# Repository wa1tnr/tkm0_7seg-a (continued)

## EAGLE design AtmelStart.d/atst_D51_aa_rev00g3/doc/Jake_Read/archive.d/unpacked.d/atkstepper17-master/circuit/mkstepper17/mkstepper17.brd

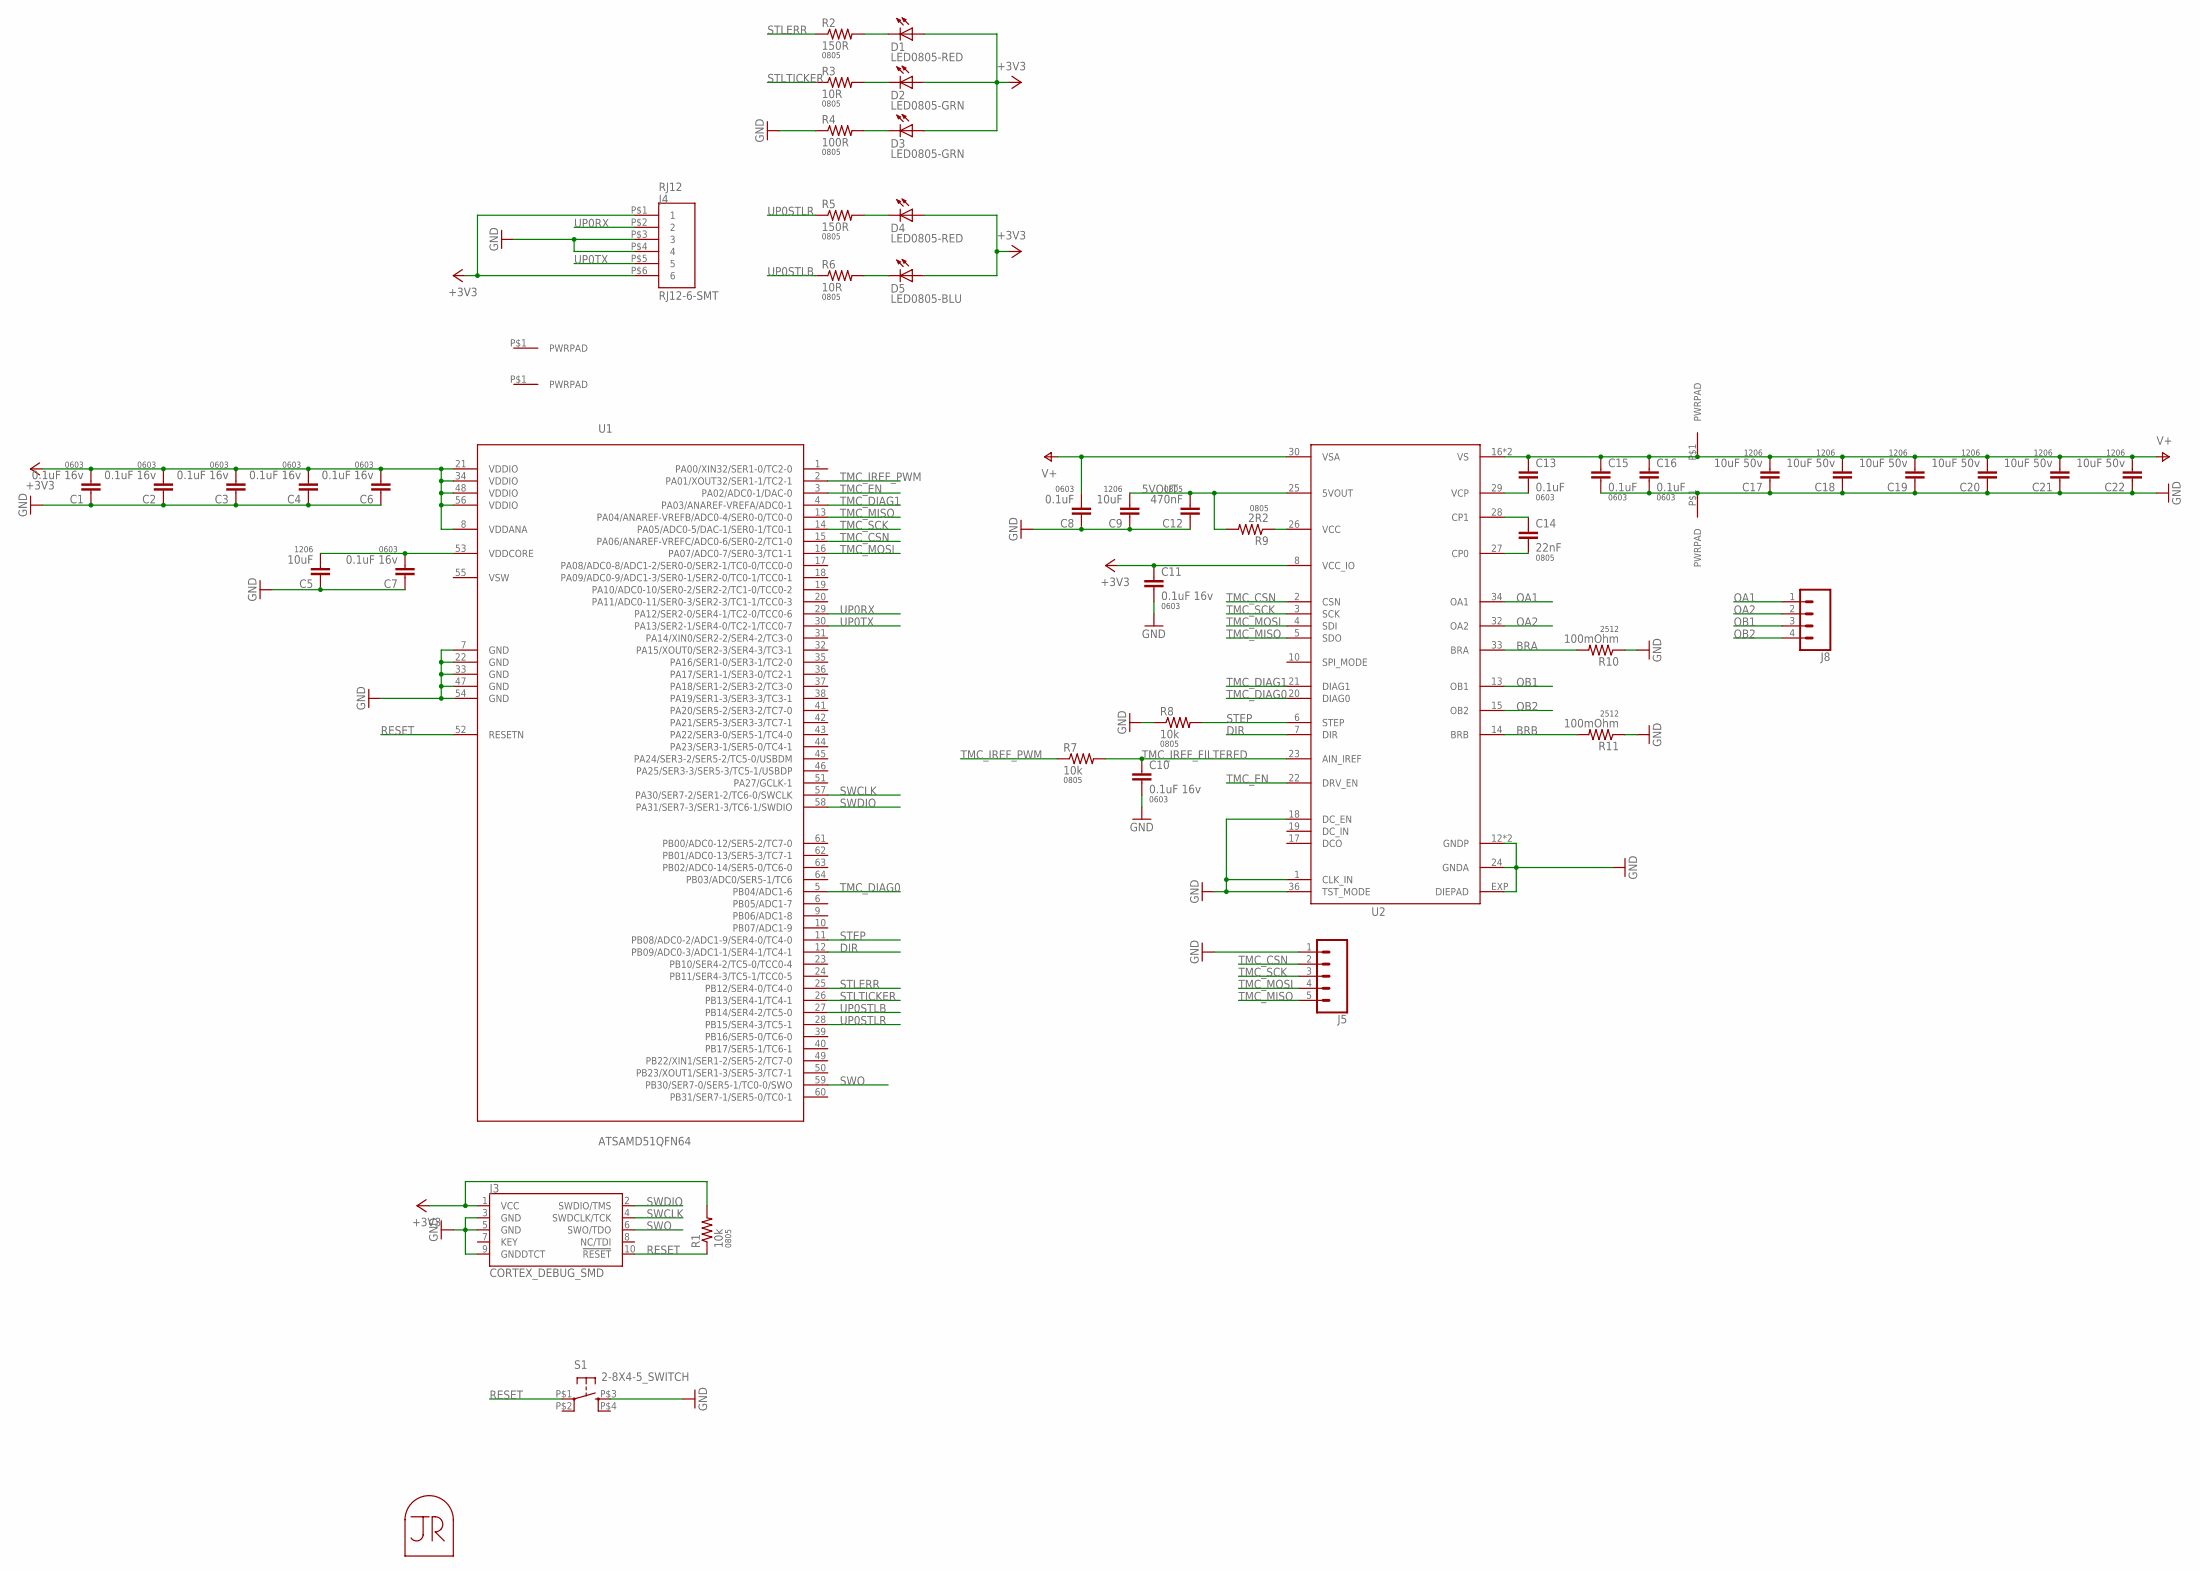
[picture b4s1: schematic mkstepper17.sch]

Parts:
C1, C2, C3, C4, C6, C7, C10, C11: 0.1uF 16v; 0603-CAP
C5, C9: 10uF; 1206
C8, C13, C15, C16: 0.1uF; 0603-CAP
C12: 470nF; 0805
C14: 22nF; 0805
C17, C18, C19, C20, C21, C22: 10uF 50v; 1206
D1, D4: LED0805-RED; LED0805
D2, D3: LED0805-GRN; LED0805
D5: LED0805-BLU; LED0805
J1, J2: PWRPADM3; PWRPAD_3-25MM
J3: CORTEX_DEBUG_SMD; SAMTECH_FTSH-105-01
J4: RJ12-6-SMT
J5: CONN_05NO_SILK; 1X05_NO_SILK
J6, J7: PWRPAD; PWRPAD_M3-PEM-MOUNT
J8: CONN_04LONGPADS; 1X04_LONGPADS
MP1: JRTOMBSTONE
R1, R7, R8: 10k; 0805
R2, R5: 150R; 0805
R3, R6: 10R; 0805
R4: 100R; 0805
R9: 2R2; 0805
R10, R11: 100mOhm; R2512
S1: 2-8X4-5_SWITCH; TACT-SWITCH-KMR6
U1: ATSAMD51QFN64; QFN-64-9X9MM
U2: TMC2130; QFN36-5X6

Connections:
5VOUT: C9.2, C12.2, R9.2, U2.25 (5VOUT)
+3V3: C1.2, C2.2, C3.2, C4.2, C6.2, C11.1, D1.1 (A), D2.1 (A), D3.1 (A), D4.1 (A), D5.1 (A), J3.1 (VCC), J4.P$1 (1), J4.P$6 (6), R1.2, U1.8 (VDDANA), U1.21 (VDDIO), U1.34 (VDDIO), U1.48 (VDDIO), U1.56 (VDDIO), U2.8 (VCC_IO)
BRA: R10.2, U2.33 (BRA)
BRB: R11.2, U2.14 (BRB)
DIR: U1.12 (PB09/ADC0-3/ADC1-1/SER4-1/TC4-1), U2.7 (DIR)
GND: C1.1, C2.1, C3.1, C4.1, C5.1, C6.1, C7.1, C8.1, C9.1, C10.2, C11.2, C12.1, C15.2, C16.2, C17.1, C18.1, C19.1, C20.1, C21.1, C22.1, J3.3 (GND), J3.5 (GND), J3.9 (GNDDTCT), J4.P$3 (3), J4.P$4 (4), J5.1, J7.P$1, R4.1, R8.1, R10.1, R11.1, S1.P$3 (S), U1.7 (GND), U1.22 (GND), U1.33 (GND), U1.47 (GND), U1.54 (GND), U2.1 (CLK_IN), U2.12 (GNDP), U2.18 (DC_EN), U2.24 (GNDA), U2.35 (GNDP), U2.36 (TST_MODE), U2.EXP (DIEPAD)
unnamed: D3.2 (C), R4.2
unnamed: D2.2 (C), R3.2
unnamed: D1.2 (C), R2.2
unnamed: C5.2, C7.2, U1.53 (VDDCORE)
unnamed: D4.2 (C), R5.2
unnamed: D5.2 (C), R6.2
unnamed: C14.2, U2.27 (CP0)
unnamed: R9.1, U2.26 (VCC)
unnamed: C14.1, U2.28 (CP1)
unnamed: C13.2, U2.29 (VCP)
OA1: J8.1, U2.34 (OA1)
OA2: J8.2, U2.32 (OA2)
OB1: J8.3, U2.13 (OB1)
OB2: J8.4, U2.15 (OB2)
RESET: J3.10 (!RESET), R1.1, S1.P$1, U1.52 (RESETN)
STEP: R8.2, U1.11 (PB08/ADC0-2/ADC1-9/SER4-0/TC4-0), U2.6 (STEP)
STLERR: R2.1, U1.25 (PB12/SER4-0/TC4-0)
STLTICKER: R3.1, U1.26 (PB13/SER4-1/TC4-1)
SWCLK: J3.4 (SWDCLK/TCK), U1.57 (PA30/SER7-2/SER1-2/TC6-0/SWCLK)
SWDIO: J3.2 (SWDIO/TMS), U1.58 (PA31/SER7-3/SER1-3/TC6-1/SWDIO)
SWO: J3.6 (SWO/TDO), U1.59 (PB30/SER7-0/SER5-1/TC0-0/SWO)
TMC_CSN: J5.2, U1.15 (PA06/ANAREF-VREFC/ADC0-6/SER0-2/TC1-0), U2.2 (CSN)
TMC_DIAG0: U1.5 (PB04/ADC1-6), U2.20 (DIAG0)
TMC_DIAG1: U1.4 (PA03/ANAREF-VREFA/ADC0-1), U2.21 (DIAG1)
TMC_EN: U1.3 (PA02/ADC0-1/DAC-0), U2.22 (DRV_EN)
TMC_IREF_FILTERED: C10.1, R7.2, U2.23 (AIN_IREF)
TMC_IREF_PWM: R7.1, U1.2 (PA01/XOUT32/SER1-1/TC2-1)
TMC_MISO: J5.5, U1.13 (PA04/ANAREF-VREFB/ADC0-4/SER0-0/TC0-0), U2.5 (SDO)
TMC_MOSI: J5.4, U1.16 (PA07/ADC0-7/SER0-3/TC1-1), U2.4 (SDI)
TMC_SCK: J5.3, U1.14 (PA05/ADC0-5/DAC-1/SER0-1/TC0-1), U2.3 (SCK)
UP0RX: J4.P$2 (2), U1.29 (PA12/SER2-0/SER4-1/TC2-0/TCC0-6)
UP0STLB: R6.1, U1.27 (PB14/SER4-2/TC5-0)
UP0STLR: R5.1, U1.28 (PB15/SER4-3/TC5-1)
UP0TX: J4.P$5 (5), U1.30 (PA13/SER2-1/SER4-0/TC2-1/TCC0-7)
V+: C8.2, C13.1, C15.1, C16.1, C17.2, C18.2, C19.2, C20.2, C21.2, C22.2, J6.P$1, U2.16 (VS), U2.30 (VSA), U2.31 (VS)

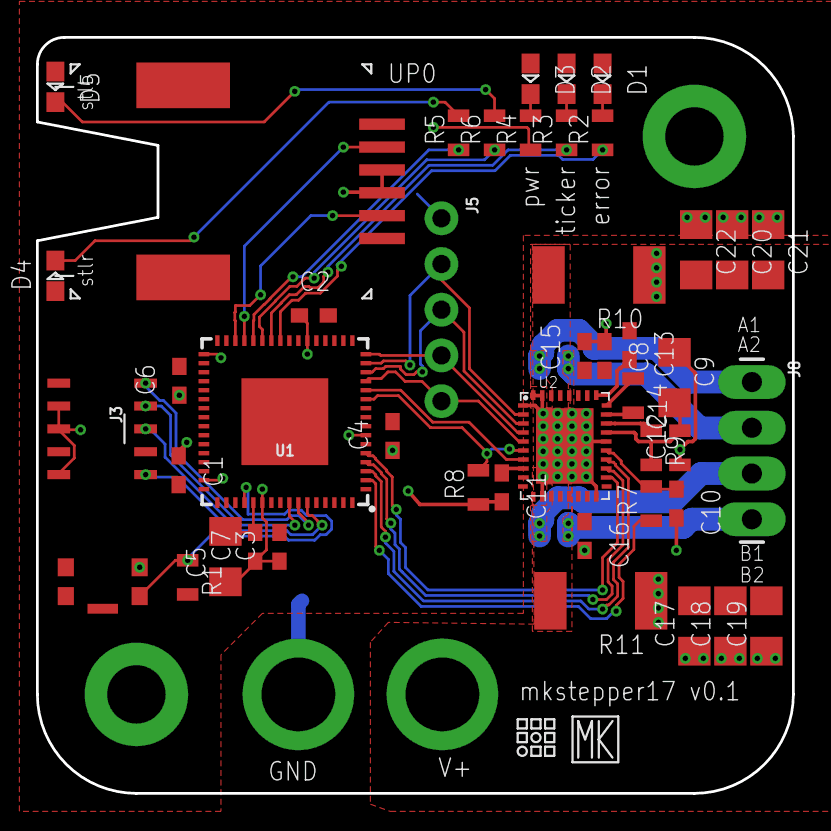
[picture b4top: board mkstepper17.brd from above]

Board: 2 copper layers, 42.0 x 42.0 mm, 52 parts (1 on the bottom side), 41 nets.

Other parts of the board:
U$5: CBA-SILK-LOGO
U$9: MK-LOGO-SILK

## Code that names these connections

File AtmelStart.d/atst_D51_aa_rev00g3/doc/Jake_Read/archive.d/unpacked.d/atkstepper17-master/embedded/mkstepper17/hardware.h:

/*
 * hardware.h
 *
 * Created: 5/18/2018 11:01:12 AM
 *  Author: Jake
 */ 

#ifndef HARDWARE_H_
#define HARDWARE_H_

#include "pin.h"
#include "ringbuffer.h"
#include "uartport.h"
#include "apaport.h"
#include "apahandler.h"

#include "spiport.h"
#include "tmc2130.h"
#include "stepper.h"

// For if-case init

#define HARDWARE_ON_PERIPHERAL_A 0x0
#define HARDWARE_ON_PERIPHERAL_B 0x1
#define HARDWARE_ON_PERIPHERAL_C 0x2
#define HARDWARE_ON_PERIPHERAL_D 0x3

// use BAUD_SYSTEM 63019 for FTDI-Limited 115200 baudrate // ~ 4.2us bit period
// use BAUD_SYSTEM 60502 for 230400 
// use BAUD_SYSTEM 55469 for 460800
// use BAUD_SYSTEM 45403 for 921600

#define BAUD_SYSTEM 63019

/*
UP0RX		PA12	SER4-1
UP0TX		PA13	SER4-0
UP0STLB		PB14	(on receive)
UP0STLR		PB15	(on transmit)
*/

ringbuffer_t up0rbrx;
ringbuffer_t up0rbtx;

uartport_t up0;

apaport_t apap0;

pin_t up0stlb; // on receive
pin_t up0stlr; // on transmit

// pointers to uartports
#define NUM_UPS 1
uartport_t *ups[NUM_UPS];

/* STATUS LIGHTS

STLTICKER		PB13
STLERR			PB12
*/

pin_t stlTicker; // green!
pin_t stlErr; // blue!

/* TIMER

*/

uint32_t overflows;

#define STEPTICKER_SYNC (TC2->COUNT32.CTRLBSET.reg = TCC_CTRLBSET_CMD_READSYNC)
#define STEPTICKER (TC2->COUNT32.COUNT.reg)

#define TICKER_SYNC (TC0->COUNT32.CTRLBSET.reg = TCC_CTRLBSET_CMD_READSYNC)
#define TICKER (TC0->COUNT32.COUNT.reg)

/* STEPPER THINGS

TMC_SCK			PA05	SER0-1
TMC_CSN			PA06	SER0-2
TMC_MOSI		PA07	SER0-3
TMC_MISO		PA04	SER0-0

TMC_IREF_PWM	PA01	TC2-1

TMC_EN			PA02
TMC_STEP		PB08
TMC_DIR			PB09

TMC_DIAG0		PB04
TMC_DIAG1		PA03

*/

spiport_t spi_tmc2130;

pin_t step_pin;
pin_t dir_pin;
pin_t en_pin;
pin_t sg_pin;

// as configured, both are open drain (active low)

pin_t diag0; // overtemp prewarning
pin_t diag1; // stall

// and write new pwm_t for duty?

tmc2130_t tmc_driver;

stepper_t stepper;


#endif /* HARDWARE_H_ */

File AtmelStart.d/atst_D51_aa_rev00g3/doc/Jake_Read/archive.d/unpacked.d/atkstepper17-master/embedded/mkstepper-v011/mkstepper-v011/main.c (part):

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
/* PINS 

STLR		PB13
STLB		PB14

NP1RX		PA12 / SER4-1
NP1TX		PA13 / SER4-0

NP2RX		PB03 / SER5-1
NP2TX		PB02 / SER5-0

TMC_SG		PB08
TMC_EN		PB07
STEP		PB08
DIR			PB09

TMC_MOSI	PA07 / SER0-3
TMC_MISO	PA04 / SER0-0
TMC_SCK		PA05 / SER0-1
TMC_CSN		PA06 / SER0-2

AS_MOSI		PA11 / SER2-3
AS_MISO		PA08 / SER2-1
AS_SCK		PA09 / SER2-0
AS_CSN		PA10 / SER2-2

*/

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	SysTick_Config(4000000);
	
	// lights
	stlb = pin_new(&PORT->Group[1], 14);
	pin_output(&stlb);
	pin_set(&stlb);
	stlr = pin_new(&PORT->Group[1], 13);
	pin_output(&stlr);
	pin_set(&stlr);
	
	// ready interrupt system
	__enable_irq();
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	apaport_reset(&apap1);
	
	// SPI
	// TMC_MOSI		PA07 / SER0-3
	// TMC_MISO		PA04 / SER0-0
	// TMC_SCK		PA05 / SER0-1
	// TMC_CSN		PA06 / SER0-2
	
	// spi
	spi_tmc = spi_new(SERCOM0, &PORT->Group[0], 4, 7, 5, 6, HARDWARE_IS_APBA, HARDWARE_ON_PERIPHERAL_D);
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	spi_init(&spi_tmc, 8, SERCOM0_GCLK_ID_CORE, 8, 0, 2, 0, 1, 1, 0);
	
	// TMC
	// STEP			PB08
	// DIR			PB09
	// EN			PB07
	// SG			PB06
	
	en_pin = pin_new(&PORT->Group[1], 7);
	sg_pin = pin_new(&PORT->Group[1], 6);
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
void SysTick_Handler(void){
	// slow ticker
	pin_toggle(&stlb);
}

void SERCOM4_0_Handler(void){
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
void SERCOM4_2_Handler(void){
	uart_rxhandler(&up0);
	pin_clear(&stlb);
}

void SERCOM5_0_Handler(void){
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
void SERCOM5_2_Handler(void){
	uart_rxhandler(&up1);
	pin_clear(&stlb);
}

void TC0_Handler(void){ // fires rarely, for counting overflows of time-ticker
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
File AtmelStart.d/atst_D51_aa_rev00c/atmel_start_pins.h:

/*
 * Code generated from Atmel Start.
 *
 * This file will be overwritten when reconfiguring your Atmel Start project.
 * Please copy examples or other code you want to keep to a separate file
 * to avoid losing it when reconfiguring.
 */
#ifndef ATMEL_START_PINS_H_INCLUDED
#define ATMEL_START_PINS_H_INCLUDED

#include <hal_gpio.h>

// SAMD51 has 14 pin functions

#define GPIO_PIN_FUNCTION_A 0
#define GPIO_PIN_FUNCTION_B 1
#define GPIO_PIN_FUNCTION_C 2
#define GPIO_PIN_FUNCTION_D 3
#define GPIO_PIN_FUNCTION_E 4
#define GPIO_PIN_FUNCTION_F 5
#define GPIO_PIN_FUNCTION_G 6
#define GPIO_PIN_FUNCTION_H 7
#define GPIO_PIN_FUNCTION_I 8
#define GPIO_PIN_FUNCTION_J 9
#define GPIO_PIN_FUNCTION_K 10
#define GPIO_PIN_FUNCTION_L 11
#define GPIO_PIN_FUNCTION_M 12
#define GPIO_PIN_FUNCTION_N 13

#define PA00 GPIO(GPIO_PORTA, 0)
#define PA01 GPIO(GPIO_PORTA, 1)
#define PA04 GPIO(GPIO_PORTA, 4)
#define PA05 GPIO(GPIO_PORTA, 5)
#define PA08 GPIO(GPIO_PORTA, 8)
#define PA09 GPIO(GPIO_PORTA, 9)
#define PA16 GPIO(GPIO_PORTA, 16)
#define PA17 GPIO(GPIO_PORTA, 17)
#define D6 GPIO(GPIO_PORTA, 18)
#define D9 GPIO(GPIO_PORTA, 19)
#define D13 GPIO(GPIO_PORTA, 23)
#define PB08 GPIO(GPIO_PORTB, 8)
#define PB09 GPIO(GPIO_PORTB, 9)
#define PB16 GPIO(GPIO_PORTB, 16)
#define PB17 GPIO(GPIO_PORTB, 17)

#endif // ATMEL_START_PINS_H_INCLUDED

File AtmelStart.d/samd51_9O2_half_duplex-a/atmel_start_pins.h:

/*
 * Code generated from Atmel Start.
 *
 * This file will be overwritten when reconfiguring your Atmel Start project.
 * Please copy examples or other code you want to keep to a separate file
 * to avoid losing it when reconfiguring.
 */
#ifndef ATMEL_START_PINS_H_INCLUDED
#define ATMEL_START_PINS_H_INCLUDED

#include <hal_gpio.h>

// SAMD51 has 14 pin functions

#define GPIO_PIN_FUNCTION_A 0
#define GPIO_PIN_FUNCTION_B 1
#define GPIO_PIN_FUNCTION_C 2
#define GPIO_PIN_FUNCTION_D 3
#define GPIO_PIN_FUNCTION_E 4
#define GPIO_PIN_FUNCTION_F 5
#define GPIO_PIN_FUNCTION_G 6
#define GPIO_PIN_FUNCTION_H 7
#define GPIO_PIN_FUNCTION_I 8
#define GPIO_PIN_FUNCTION_J 9
#define GPIO_PIN_FUNCTION_K 10
#define GPIO_PIN_FUNCTION_L 11
#define GPIO_PIN_FUNCTION_M 12
#define GPIO_PIN_FUNCTION_N 13

#define PA16 GPIO(GPIO_PORTA, 16)
#define PA18 GPIO(GPIO_PORTA, 18)
#define PA19 GPIO(GPIO_PORTA, 19)
#define PA22 GPIO(GPIO_PORTA, 22)
#define PA23 GPIO(GPIO_PORTA, 23)
#define PB14 GPIO(GPIO_PORTB, 14)

#endif // ATMEL_START_PINS_H_INCLUDED

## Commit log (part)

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2018-06-30 CircuitPython for RPi - installation report - 30 June 2018 - aa new file: new_circuit_python_linux_RPI_installation_report_aa.txt
2018-07-30 Atmel Start SAMD51 new file: AtmelStart.d/atst_D51_aa_rev00c/0-Distrib.d/atst_51_aa_rev00c.zip new file: AtmelStart.d/atst_D51_aa_rev00c/AtmelStart.env_conf new file: AtmelStart.d/atst_D51_aa_rev00c/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
2018-07-30 Circuit Python Meeting notes wrt SAMD51 GPIO inop - @nis - 30 July 2018 new file: cp_meeting_SAMD51_atmel_start.txt
2018-07-30 PA17 old cruft SAMD21 - changed to SAMD51 (comments only) modified: gpio_local.c
2018-07-30 edits. 'Approaches' new section at bottom. modified: AtmelStart.d/cp_meeting_SAMD51_atmel_start.txt
2018-07-30 Tried old bossac - definitely not the right path. modified: scripts/_bossac_local.sh Maybe download a bossac and compile it, or move on to a different code upload scheme.
2018-07-30 gitignore new file: .gitignore
2018-07-30 On newest tree - gitignore new file: .gitignore
2018-07-30 Newest Atmel Start code - unmodified to begin with. More to follow. new file: driver_init.c new file: driver_init.h
2018-07-30 main.c instantiated from Atmel Start. new file: main.c
2018-07-30 pins.h will have needed pointer to PA23 (D13 in Arduino-speak) new file: atmel_start_pins.h
2018-07-30 The .atzip file (renamed) generating all this. new file: 0-Distrib.d/atst_D51_aa_rev00d.zip
2018-07-30 Unmodified Makefile new file: Makefile
2018-07-30 Unmodified system__.c file new file: system_samd51.c
2018-07-30 Factory config directory - peripheral_clk_config.h especially new file: config/hpl_dmac_config.h new file: config/hpl_gclk_config.h new file: config/hpl_mclk_config.h new file: config/hpl_osc32kctrl_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
2018-07-30 atstart new file: atmel_start_config.atstart
2018-07-30 Two more AtmelStart files new file: AtmelStart.env_conf new file: AtmelStart.gpdsc
2018-07-30 HAL abstraction layer. Atmel Start generated new file: include/hal_atomic.h new file: include/hal_delay.h new file: include/hal_gpio.h new file: include/hal_init.h new file: include/hal_io.h new file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
2018-07-30 Hotel Papa Lima new file: core/hpl_core_m4.c new file: core/hpl_core_port.h new file: core/hpl_init.c new file: dmac/hpl_dmac.c new file: gclk/hpl_gclk.c new file: gclk/hpl_gclk_base.h new file: mclk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
2018-07-30 include/component tree - all new file: component/ac.h new file: component/adc.h new file: component/aes.h new file: component/can.h new file: component/ccl.h new file: component/cmcc.h new file: comp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
2018-07-30 include/instance tree new file: instance/ac.h new file: instance/adc0.h new file: instance/adc1.h new file: instance/aes.h new file: instance/can0.h new file: instance/can1.h new file: instance/ccl.h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
2018-07-30 include/*.h no subdirectories in this one commit new file: component-version.h new file: sam.h new file: samd51.h new file: samd51g18a.h new file: samd51g19a.h new file: samd51j18a.h new file: samd51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
2018-07-30 gcc new file: gcc/samd51j19a_flash.ld new file: gcc/samd51j19a_sram.ld new file: gcc/startup_samd51.c
2018-07-30 Hotel Romeo India - hri new file: hri/hri_ac_d51.h new file: hri/hri_adc_d51.h new file: hri/hri_aes_d51.h new file: hri/hri_ccl_d51.h new file: hri/hri_cmcc_d51.h new file: hri/hri_d51.h new file: h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
2018-07-30 Not used (no harm in using it) new file: armcc/Makefile
2018-07-30 CMSIS - very light, considering new file: CMSIS/Documentation/Core/html/index.html new file: CMSIS/Include/arm_common_tables.h new file: CMSIS/Include/arm_const_structs.h new file: CMSIS/Include/arm_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
2018-07-30 Not ready yet new file: WAIT
2018-07-30 Linker with 0x4000 ORIGIN new file: samd51j19a_flash_with_bootloader.ld
2018-07-30 unnoticed stragglers added modified: .gitignore
2018-07-30 A couple more ignores added modified: .gitignore
2018-07-30 surprise! may be onto something new file: aha__000a.txt
2018-07-30 local scripts - not part of Atmel Start new file: scripts/_bossac_local.sh new file: scripts/_bossac_local.sh--older new file: scripts/_compile.sh new file: scripts/samd51j19a_flash_with_bootloader.ld
2018-07-30 System Clean of errors. Running now. Go ahead and compile this. deleted: WAIT
2018-07-30 Do not turn it off modified: driver_init.c
2018-07-30 object dump syntax new file: gcc/scripts/objdumper.sh
2018-07-30 gpio_local.c object and .d files modified: gcc/Makefile
2018-07-30 kept somewhat short. Basic blinkie stuff. May be disabled. modified: main.c
2018-07-30 include file for local gpio new file: gpio_local.h
2018-07-30 Nice to have a copy handy new file: gcc/Makefile__ORIG__
2018-07-30 First objdump of this program. new file: gcc/Log.d/objdump.00aa-
2018-07-31 modified: atmel_start_pins.h modified: gpio_local.c modified: gpio_local.h modified: main.c
2018-07-31 I seem to have done a GPIO program. LED stayed on (Metro M4 Express). new file: Makefile new file: gcc/samd51j19a_flash_with_bootloader.ld SMOKING GUN
2018-07-31 There's no Atmel Start specification for an Adafruit board new file: main.c new file: 0-Distrib.d/flish-flash-hhh.zip new file: AtmelStart.env_conf new file: AtmelStart.gpdsc new file: CMSIS/Document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
2018-07-31 new file: objdump_already_available.txt
2018-07-31 new file: xMakefile new file: ../xmain.cx
2018-07-31 new file: ../.gitignore
2018-07-31 modified: Makefile modified: gcc/samd51j19a_flash_with_bootloader.ld
2018-07-31 On the road to a GOOD CLOCK setup - was the problem all along. modified: main.c
2018-07-31 Removed commented includes. modified: main.c
2018-07-31 Empty timing loops modified: main.c
2018-07-31 Renamed pin raises to reflect both are D13 - on different target boards modified: main.c
2018-07-31 New names for these. modified: gpio_local.h
2018-07-31 Origination of recent name changes begins here. modified: gpio_local.c
2018-07-31 modified: gpio_local.h
2018-07-31 dash to understore name change - trivial modified: gpio_local.c
2018-07-31 More name changes. Undercores and such. modified: main.c
2018-07-31 This and the next edits remove hidden ^M chars from this important file
2018-07-31 More ctrl M modified: samd51j19a_flash_with_bootloader.ld
2018-07-31 Ctrl M removals continue .. modified: samd51j19a_flash_with_bootloader.ld
2018-07-31 More edits like them modified: samd51j19a_flash_with_bootloader.ld
2018-07-31 And more of those edits .. modified: samd51j19a_flash_with_bootloader.ld
2018-07-31 More edits modified: samd51j19a_flash_with_bootloader.ld
2018-07-31 More control ems modified: samd51j19a_flash_with_bootloader.ld
2018-07-31 Large changeset - nothing but s/^M// here no worries modified: samd51j19a_flash_with_bootloader.ld
2018-07-31 [SOLVED] there was no functioning CLOCK. Now there is. ;) new file: this_was_the_problem_.c_
2018-07-31 This is a complete application for ATSAMD51J19A new file: complete_Atmel_Start_SAMD51_Application
2018-07-31 Title edits - not a working file but a copy of one to be merged in. modified: this_was_the_problem_.c_
2018-07-31 Ghost-towned this directory. All gone/cut to base. For the moment, at least. modified: hpl_dmac_config.h modified: hpl_gclk_config.h modified: hpl_mclk_config.h modified: hpl_nvmctrl_config.h modifie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
2018-07-31 Here in, there, is that of which we was. CLOCK. modified: main.c
2018-07-31 wouldn't leave ya toltali stranded new file: real_config_/hpl_dmac_config.h new file: real_config_/hpl_gclk_config.h new file: real_config_/hpl_mclk_config.h new file: real_config_/hpl_nvmctrl_config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
2018-07-31 Untested - needs to be verified as complete (relatively). new file: UNTESTED_FINAL
2018-07-31 Preserved - will overwrite its namesake with the current good one from the working tree. new file: samd51j19a_flash_with_bootloader.ld__OLDER_
2018-07-31 Untested - should be a good copy of the working one in the active file tree. modified: samd51j19a_flash_with_bootloader.ld
2018-07-31 Now with upstream Author's source code snippet for the clock setup modified: main.c
2018-07-31 Upstream sources. Some items truncated. Convenience copy, only. new file: .gitignore new file: README.md new file: cad/backmount-3dp-01.gcode new file: cad/backmount-3dp-01.stl new file: circuit/READ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
2018-07-31 Credits fashioned from a main.c file. Who knew? new file: main.c_credits_and_snips.txt
2018-07-31 More credits/sources stuph. Jake Read is the author of the outside clock stuph. new file: ../main.c__This_One__
2018-07-31 List of md5sums for the directory this file is found in under this name. new file: md5sums.txt
2018-07-31 a find document listing what unix find found (fine?) new file: find_dot.txt
2018-07-31 Truncated files (has the output of unix 'date' in them). new file: atkstep-17_d.tar.bz2--TRUNCATED new file: atkstepper17-master.tar.bz2--TRUNCATED
2018-07-31 new file: AtmelStart.bin new file: AtmelStart.elf new file: AtmelStart.hex new file: AtmelStart.lss new file: AtmelStart.map new file: ls-la.txt
2018-07-31 gitignore file new file: .gitignore
2018-07-31 Last Commit .. possibly .. for today. A gitignore file. modified: .gitignore
2018-07-31 Soft link to the current vesion of the program. And a simpler sign (posted as a file) to do the same. new file: Current.d new file: USE.atst_D51_aa_rev00g3.txt
2018-07-31 Working SAMD51J19A Metro M4 Express Blinkie in Bare Metal. 1600 bytes. Tested good! Consider it published in the sandboxx, temporarily. new file: TESTED_GOOD
2018-07-31 deleted: UNTESTED_FINAL
2018-07-31 SAMD51J19A bare metal demo program ARM compiler. July 2018 wa1tnr new file: .touchfile
2018-07-31 ATSAMD51 bare metal demo - Instructions (terse). new file: INSTRUX.txt
2018-10-09 Based on Charley Shattuck's interpreter for Feather M0:
    On branch testing-cc
    new file: simple_adrs_prn.ino
2018-10-11 On branch testing-dd new file: arduino/Arduino.h new file: arduino/Client.h new file: arduino/HardwareSerial.h new file: arduino/IPAddress.cpp new file: arduino/IPAddress.h new file: arduino/Print.cp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
2018-11-27 On branch shift_reg_branch-aa- new file: shift_register_bb.ino
2018-11-27 On branch shift_reg_branch-aa- modified: shift_register_bb.ino
2018-11-27 On branch shift_reg_branch-aa- new file: config.h
2018-11-27 On branch shift_reg_branch-aa- new file: dotstar.h
2018-11-27 On branch shift_reg_branch-aa- new file: dotstar.cpp new file: dotstar.h
2018-11-27 On branch shift_reg_branch-aa- new file: shift_register_cc.ino
2018-11-27 On branch shift_reg_branch-aa- modified: shift_register_cc.ino
2018-11-27 new file: shift_register_cc/config.h deleted: t.d/shift_register_cc/config.h deleted: t.d/shift_register_cc/shift_register_cc.ino deleted: t.d/shift_register_cc/src/periph/dotstar.cpp deleted: t.d/sh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
2018-11-27 On branch shift_reg_branch-aa- deleted: t.d/shift_register_cc/config.h deleted: t.d/shift_register_cc/shift_register_cc.ino deleted: t.d/shift_register_cc/src/periph/dotstar.cpp deleted: t.d/shift_re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
2018-11-27 fairly complete demo.
    wants: parser (to change the
    message during runtime)
    On branch shift_reg_branch-aa-
    modified: shift_register_cc.ino
2018-11-28 somewhat related python on desktop PC - turtle graphics seven segment display - trials
    On branch shift_reg_branch-aa-
    new file: draw_7_seg_turtle_aa0aa.py
2018-11-28 nicer demo features On branch shift_reg_branch-aa- modified: config.h
2018-11-28 Interesting diff to look at for changes made On branch shift_reg_branch-aa- modified: shift_register_cc.ino
2018-11-28 renamed some routines to 'encode_*' On branch shift_reg_branch-aa- modified: shift_register_cc.ino
2018-11-28 renamed _puteye() to _flash_digit() On branch shift_reg_branch-aa- modified: shift_register_cc.ino
2019-04-27 Mass deletes On NEW BRANCH shift_reg_branch-bb- deleted: .touchfile deleted: ArduinoIDE/IDE/p.arduino15/packages/adafruit/hardware/samd/1.2.1/cores/arduino/Arduino.h deleted: ArduinoIDE/IDE/p.arduino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
2019-04-27 New file: README.md On branch master new file: README.md
2019-04-27 NEW BRANCH shift_reg_branch-dd-
    Timestamped the readme file to instantiate this branch.
    modified: README.md
2019-04-27 NEW BRANCH shift_reg_branch-ee- modified: README.md
2019-04-27 On branch shift_reg_branch-ee- modified: README.md
